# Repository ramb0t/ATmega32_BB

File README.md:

# ATmega32_BB
My ATmega32 Breakout Board for Bread Board

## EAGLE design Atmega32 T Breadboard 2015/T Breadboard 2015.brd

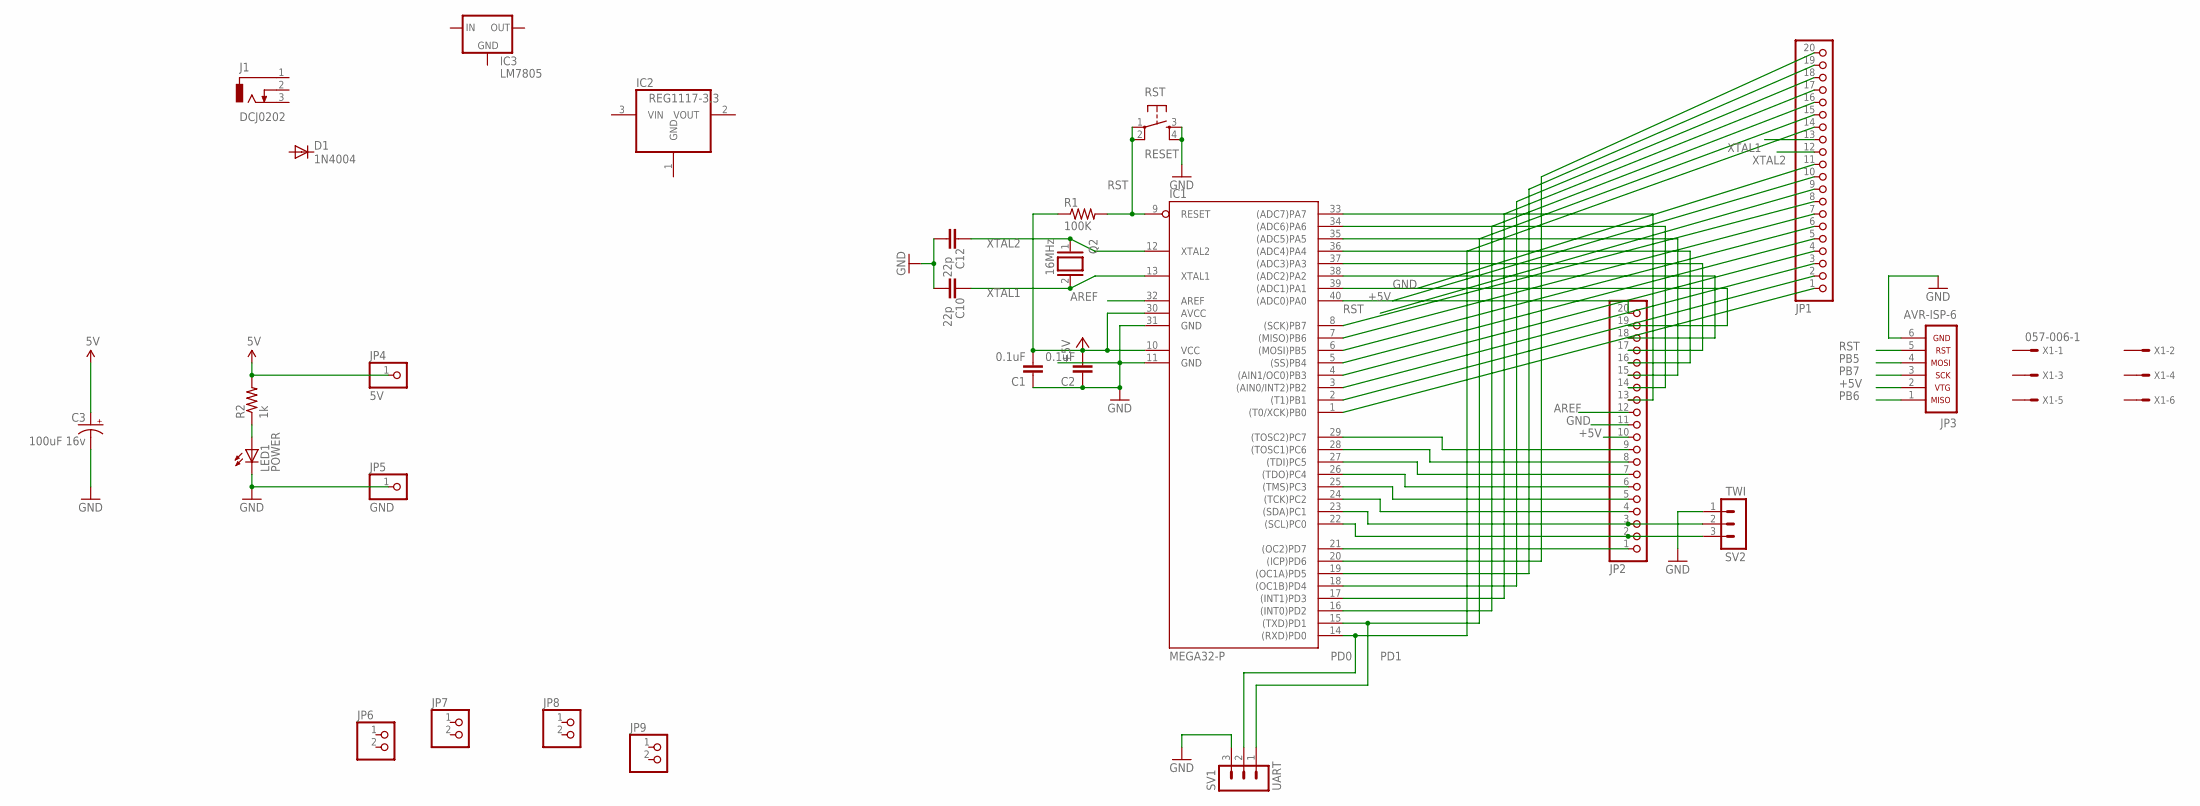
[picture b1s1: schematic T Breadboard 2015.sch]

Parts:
C1, C2: 0.1uF; CAP-PTH-SMALL2
C3: 100uF 16v; CPOL-RADIAL-100UF-25V
C10, C12: 22p; C025-030X050
D1: 1N4004; DO41-10
IC1: MEGA32-P; DIL40
IC2: REG1117-3.3; SOT223
IC3: LM7805; TO220-IGO
J1: DCJ0202
JP1, JP2: PINHD-1X20; 1X20
JP3: AVR-ISP-6
JP4: 5V; 1X01
JP5: GND; 1X01
JP6, JP7, JP8, JP9: PINHD-1X2; 1X02
LED1: POWER; LED3MM
Q2: 16MHz; QS
R1: 100K; 0207/10
R2: 1k; AXIAL-0.3
RST: RESET; TACTILE-PTH
SV1: UART; MA03-1
SV2: TWI; MA03-1
X1: 057-006-1

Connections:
+5V: C1.2, C2.2, C3.1 (+), IC1.10 (VCC), IC1.30 (AVCC), JP1.10, JP2.10, JP3.2, JP4.1, R1.1, R2.P$2 (2)
AREF: IC1.32 (AREF), JP2.12
GND: C1.1, C2.1, C3.2 (-), C10.1, C12.1, IC1.11 (GND), IC1.31 (GND), IC2.1 (GND), JP1.11, JP2.11, JP3.6, JP5.1, LED1.K (C), RST.3, RST.4, SV1.3, SV2.1
LED1: LED1.A, R2.P$1 (1)
unnamed: IC1.1 ((T0/XCK)PB0), JP1.1
unnamed: IC1.20 ((ICP)PD6), JP1.20
unnamed: IC1.2 ((T1)PB1), JP1.2
unnamed: IC1.3 ((AIN0/INT2)PB2), JP1.3
unnamed: IC1.4 ((AIN1/OC0)PB3), JP1.4
unnamed: IC1.5 ((SS)PB4), JP1.5
unnamed: IC1.21 ((OC2)PD7), JP2.1
unnamed: IC1.16 ((INT0)PD2), JP1.16
unnamed: IC1.17 ((INT1)PD3), JP1.17
unnamed: IC1.18 ((OC1B)PD4), JP1.18
unnamed: IC1.19 ((OC1A)PD5), JP1.19
unnamed: IC1.22 ((SCL)PC0), JP2.2, SV2.3
unnamed: IC1.23 ((SDA)PC1), JP2.3, SV2.2
unnamed: IC1.24 ((TCK)PC2), JP2.4
unnamed: IC1.25 ((TMS)PC3), JP2.5
unnamed: IC1.26 ((TDO)PC4), JP2.6
unnamed: IC1.27 ((TDI)PC5), JP2.7
unnamed: IC1.28 ((TOSC1)PC6), JP2.8
unnamed: IC1.29 ((TOSC2)PC7), JP2.9
unnamed: IC1.33 ((ADC7)PA7), JP2.13
unnamed: IC1.34 ((ADC6)PA6), JP2.14
unnamed: IC1.35 ((ADC5)PA5), JP2.15
unnamed: IC1.36 ((ADC4)PA4), JP2.16
unnamed: IC1.37 ((ADC3)PA3), JP2.17
unnamed: IC1.38 ((ADC2)PA2), JP2.18
unnamed: IC1.39 ((ADC1)PA1), JP2.19
unnamed: IC1.40 ((ADC0)PA0), JP2.20
PB5: IC1.6 ((MOSI)PB5), JP1.6, JP3.4
PB6: IC1.7 ((MISO)PB6), JP1.7, JP3.1
PB7: IC1.8 ((SCK)PB7), JP1.8, JP3.3
PD0: IC1.14 ((RXD)PD0), JP1.14, SV1.2
PD1: IC1.15 ((TXD)PD1), JP1.15, SV1.1
RST: IC1.9 (RESET), JP1.9, JP3.5, R1.2, RST.1, RST.2
XTAL1: C10.2, IC1.13 (XTAL1), JP1.13, Q2.2
XTAL2: C12.2, IC1.12 (XTAL2), JP1.12, Q2.1

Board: 2 copper layers, 27 parts (0 on the bottom side), 39 nets, no tracks yet.

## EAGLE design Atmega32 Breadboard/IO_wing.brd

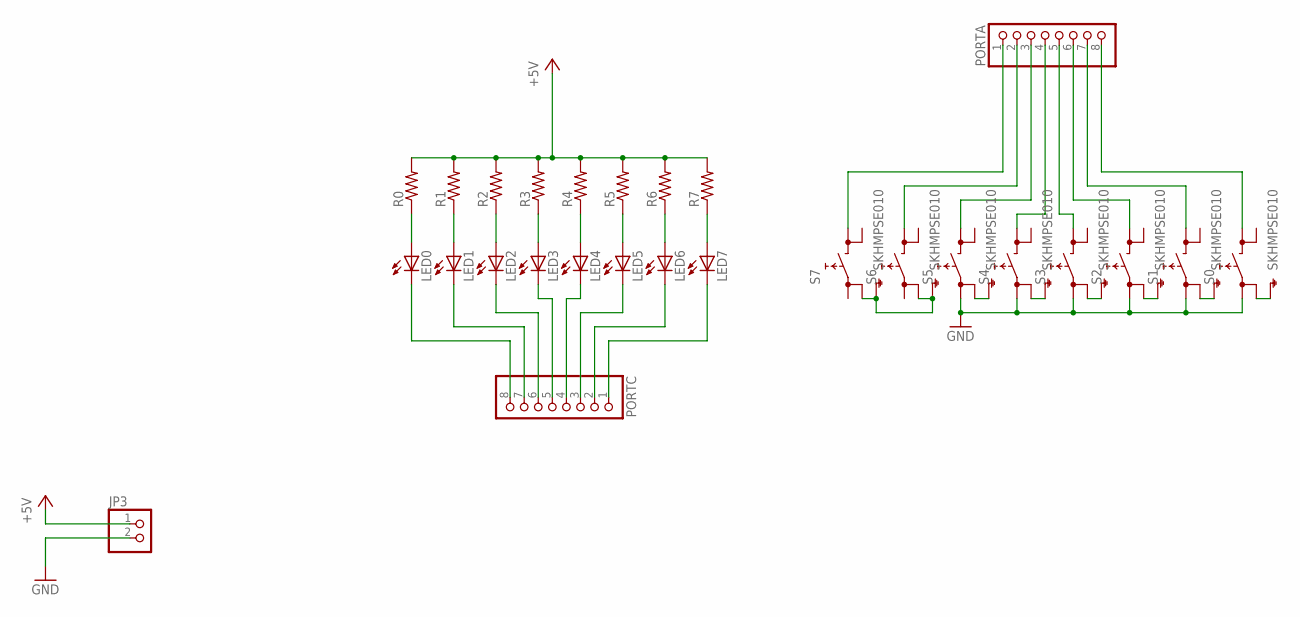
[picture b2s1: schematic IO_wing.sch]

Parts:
JP3: PINHD-1X2; 1X02
LED0, LED1, LED2, LED3, LED4, LED5, LED6, LED7: LEDCHIP-LED0805; CHIP-LED0805
PORTA: PINHD-1X8; 1X08
PORTC: PINHD-1X8; 1X08
R0, R1, R2, R3, R4, R5, R6, R7: R-US_R0805; R0805
S0, S1, S2, S3, S4, S5, S6, S7: SKHMPSE010; SKHMPXE010

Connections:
+5V: JP3.1, R0.2, R1.2, R2.2, R3.2, R4.2, R5.2, R6.2, R7.2
GND: JP3.2, S0.1 (1.1), S1.1 (1.1), S2.1 (1.1), S3.1 (1.1), S4.1 (1.1), S5.1 (1.1)
unnamed: PORTA.4, S4.3 (2.1)
unnamed: PORTA.5, S3.3 (2.1)
unnamed: LED0.A, R0.1
unnamed: LED1.A, R1.1
unnamed: LED2.A, R2.1
unnamed: LED3.A, R3.1
unnamed: LED4.A, R4.1
unnamed: LED5.A, R5.1
unnamed: LED6.A, R6.1
unnamed: LED7.A, R7.1
unnamed: LED2.C, PORTC.6
unnamed: LED3.C, PORTC.5
unnamed: LED4.C, PORTC.4
unnamed: LED1.C, PORTC.7
unnamed: LED0.C, PORTC.8
unnamed: LED5.C, PORTC.3
unnamed: LED6.C, PORTC.2
unnamed: LED7.C, PORTC.1
unnamed: PORTA.3, S5.3 (2.1)
unnamed: PORTA.2, S6.3 (2.1)
unnamed: PORTA.1, S7.3 (2.1)
unnamed: PORTA.6, S2.3 (2.1)
unnamed: PORTA.7, S1.3 (2.1)
unnamed: PORTA.8, S0.3 (2.1)
unnamed: S6.2 (1.2), S6.5 (SH), S7.2 (1.2), S7.5 (SH)
unnamed: S5.2 (1.2), S5.5 (SH)
unnamed: S1.2 (1.2), S1.5 (SH)
unnamed: S3.2 (1.2), S3.5 (SH)
unnamed: S2.2 (1.2), S2.5 (SH)
unnamed: S0.2 (1.2), S0.5 (SH)
unnamed: S4.2 (1.2), S4.5 (SH)

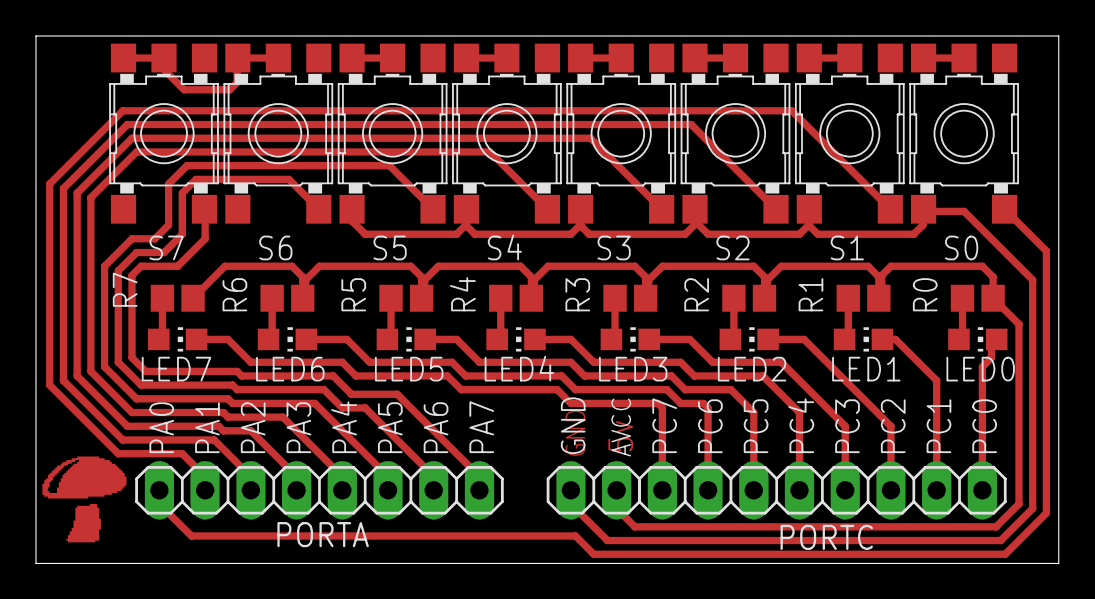
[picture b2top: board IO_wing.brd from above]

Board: 2 copper layers, 56.8 x 29.3 mm, 27 parts (0 on the bottom side), 33 nets.

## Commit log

2015-06-28 First Commit moving to SC
2016-11-17 125k osc messing around
